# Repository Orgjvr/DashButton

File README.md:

# DashButton
This is a IOT button which sends a MQTT message with the VCC voltage when pressed. Optimised for battery use.

I run it on an ESP-01 (actually an ESP8266 with the first form factor). It needs minimal connections, and works great from a 3.7V LiPo battery with an inline diode to drop the voltage a bit to ensure the safety of the ESP8266. 

I have multiple of these buttons in my home, and a cheap no-name 18650 battery last more than a year. Of course if you are going to do thousands of button presses, the battery will need replacement sooner. I do have some stats about the amount of button presses, but I need to analyse it, as the original version of the code, went into an infinite loop if it could not connect to either the Wifi, or the MQTT server. This depleted the batteries in no amount of time :) The newer version, will limit the amount of attempted connections, and if it could not connect, go back to sleep.

Todo:
  Add some photos of the development button.
  Get info of amount of button presses.

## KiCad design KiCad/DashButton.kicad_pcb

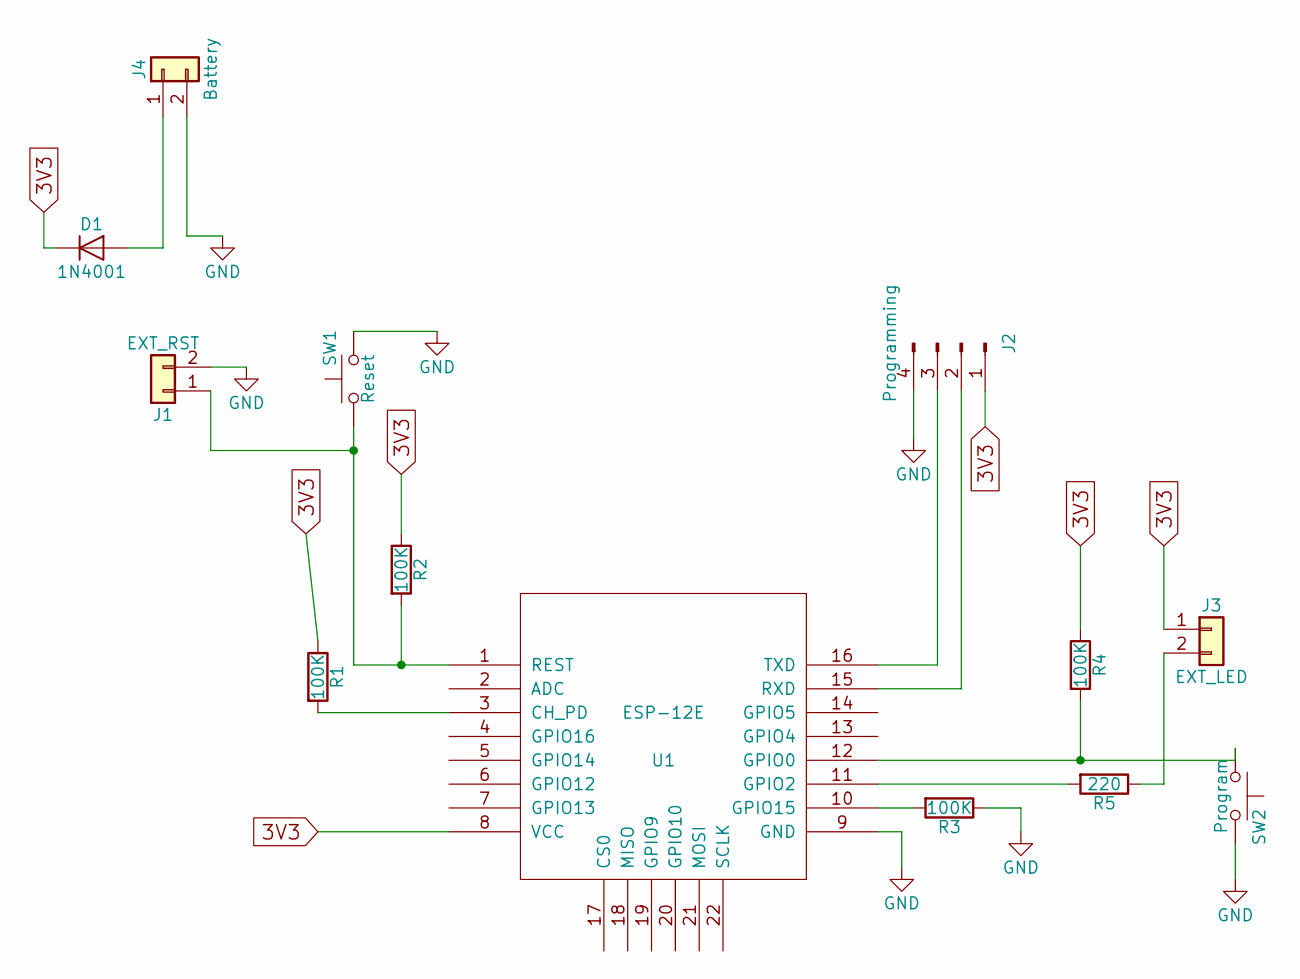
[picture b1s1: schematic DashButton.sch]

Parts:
D1: 1N4001; D_DO-41_SOD81_P7.62mm_Horizontal
J1: EXT_RST; Pin_Header_Straight_1x02_Pitch2.54mm
J2: Programming; Pin_Header_Straight_1x04_Pitch2.54mm
J3: EXT_LED; Pin_Header_Straight_1x02_Pitch2.54mm
J4: Battery; Pin_Header_Straight_1x02_Pitch2.54mm
R1, R2, R3, R4: 100K; R_Axial_DIN0411_L9.9mm_D3.6mm_P7.62mm_Vertical
R5: 220; R_Axial_DIN0411_L9.9mm_D3.6mm_P7.62mm_Vertical
SW1: Reset; SW_PUSH_6mm
SW2: Program; SW_PUSH_6mm
U1: ESP-12E; ESP-12E_SMD

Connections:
3V3: D1.1 (K), J2.1, J3.1, R1.1, R2.1, R4.1, U1.8 (VCC)
GND: J1.2, J2.4, J4.2, R3.1, SW1.2, SW2.2, U1.9 (GND)
unnamed: D1.2 (A), J4.1
unnamed: J1.1, R2.2, SW1.1, U1.1 (REST)
unnamed: J2.2, U1.15 (RXD)
unnamed: J2.3, U1.16 (TXD)
unnamed: J3.2, R5.1
unnamed: R1.2, U1.3 (CH_PD)
unnamed: R3.2, U1.10 (GPIO15)
unnamed: R4.2, SW2.1, U1.12 (GPIO0)
unnamed: R5.2, U1.11 (GPIO2)

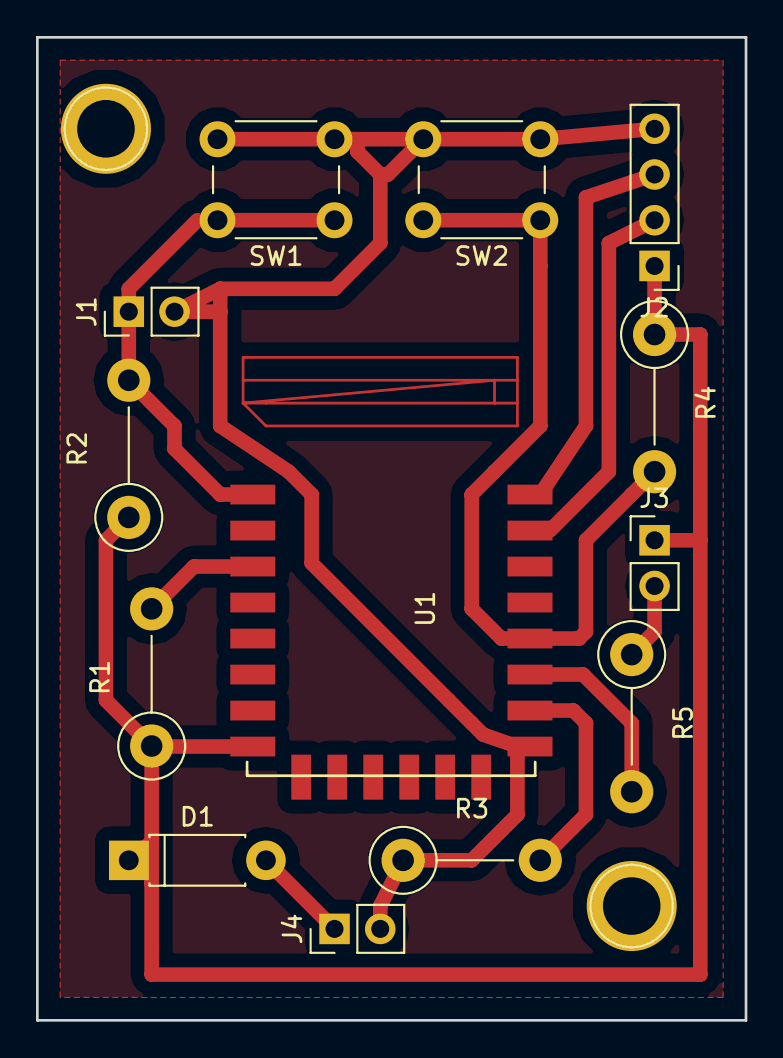
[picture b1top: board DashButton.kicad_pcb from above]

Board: 2 copper layers, 39.4 x 54.6 mm, 13 parts (0 on the bottom side), 11 nets.

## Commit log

2019-12-08 This is version 1.0 of the working DashButton
2019-12-08 Added some Kicad designs
